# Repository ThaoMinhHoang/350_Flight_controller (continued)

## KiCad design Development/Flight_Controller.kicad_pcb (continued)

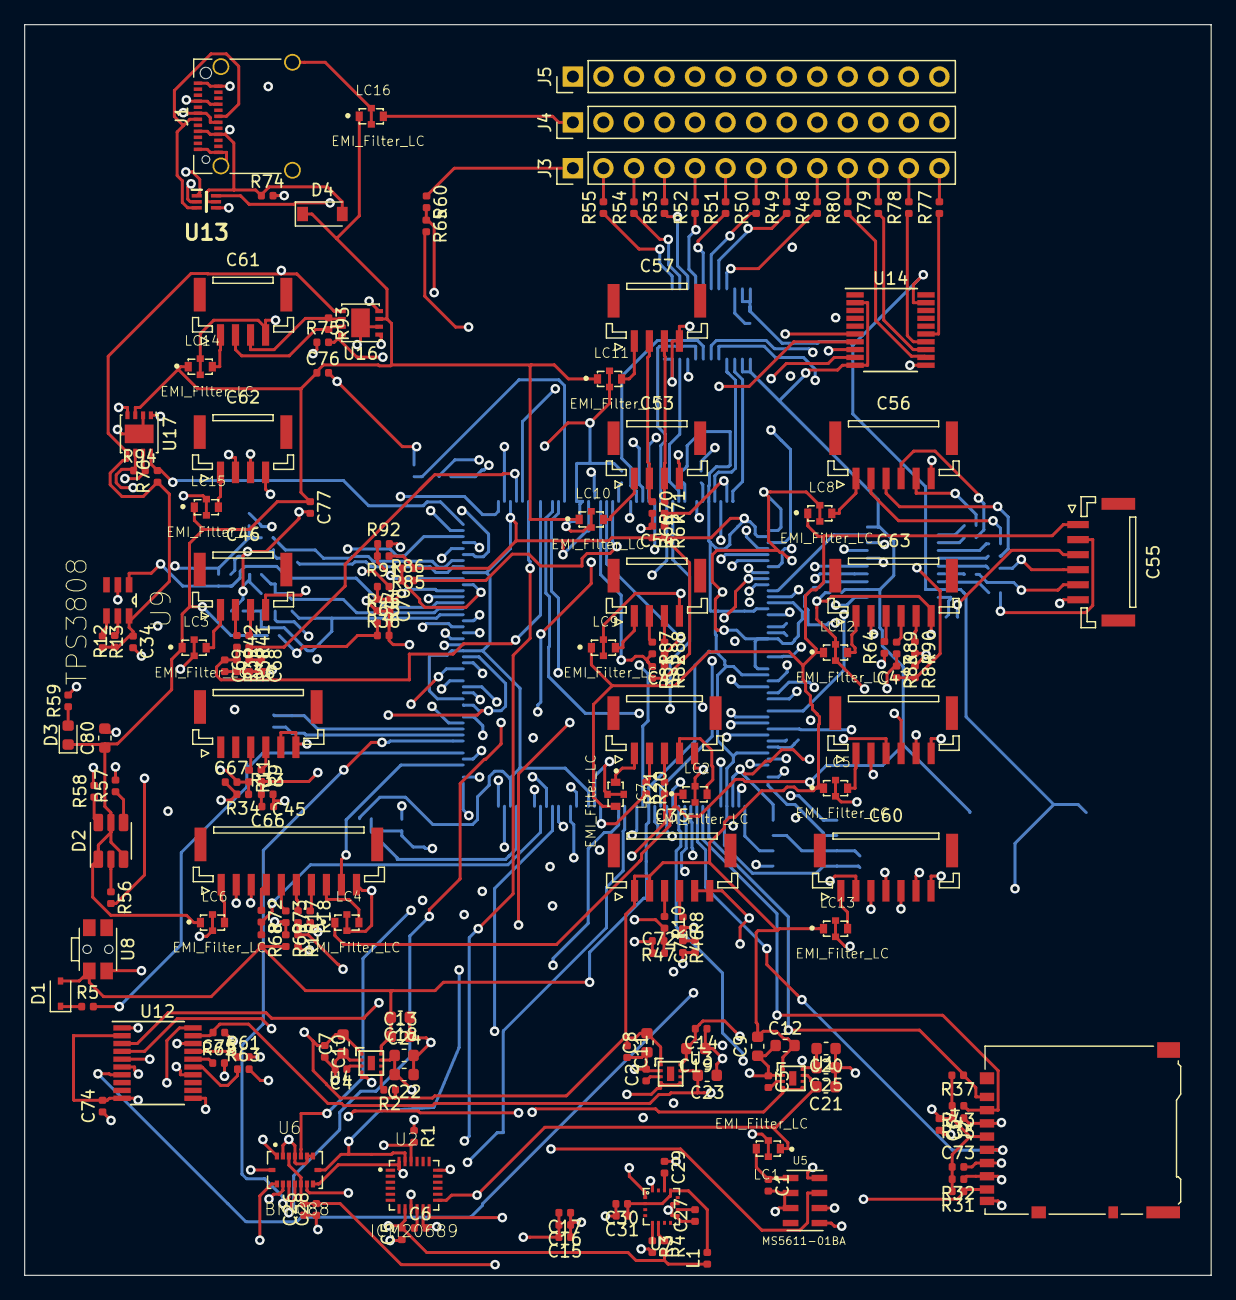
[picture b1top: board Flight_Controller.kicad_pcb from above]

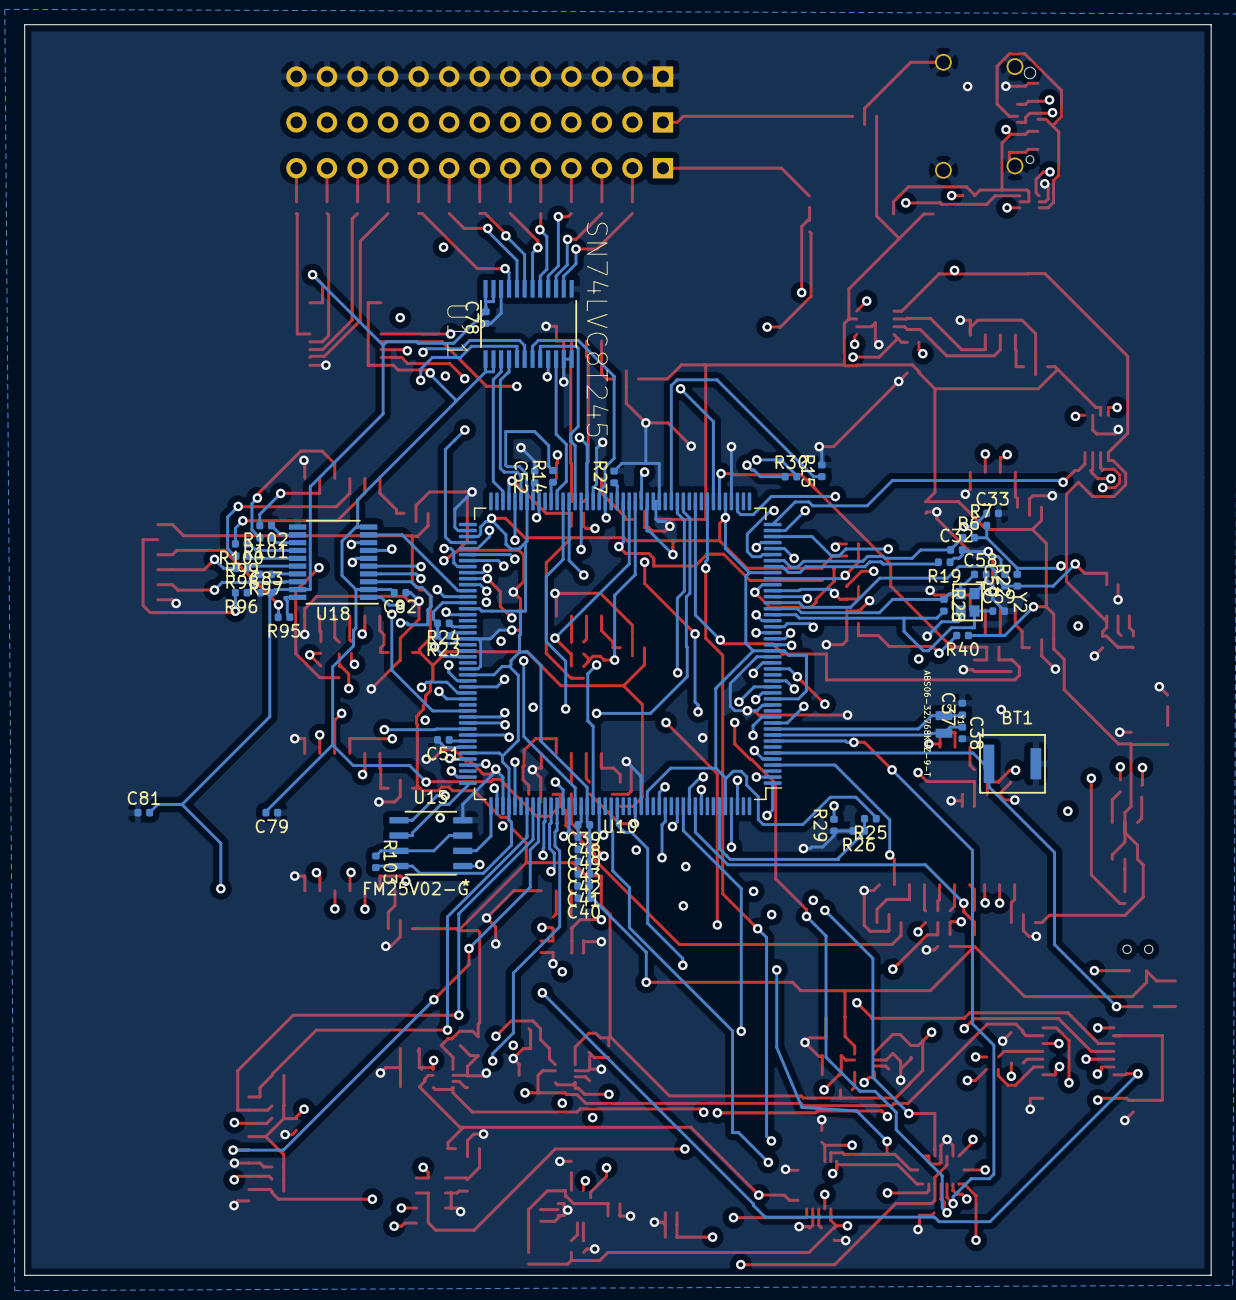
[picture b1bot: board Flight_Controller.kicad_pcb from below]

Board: 4 copper layers, 98.7 x 104.0 mm, 233 parts (52 on the bottom side), 236 nets.

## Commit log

2019-07-04 Create Magnetometer
2019-07-04 Magnetometer update
2019-07-05 Main Processor Update
2019-07-07 Update schematic to include all labels
2019-07-07 Added a couple of notes
2019-07-07 Added development schematics
    - Includes new connector symbols
    - Includes STM32F765IIT6 in schematic
    - Includes labeled connectors in schematic
2019-07-07 README revision
2019-07-15 Begun labelling connectors with pinout document
2019-08-01 ICM20689 Kidfile
2019-08-08 BMI088
2019-08-08 Power Supply
    Power supply for pixhawk 4 along with a few external power connectors and connections
2019-08-08 update IST8310, DPS422
2019-08-08 Hope for the best
2019-08-08 Hole for the best 2
2019-08-12 Updated Wiring
    - 3 Sensors connected, some might need to change. Definitely needs to be double-checked at some point.
    - All labels are now global
2019-08-12 Crystal oscillator circuit added
2019-08-13 wiring updates
2019-08-14 Updated power connections
    All power components have been connected to the appropriate places
2019-08-15 Organised layout of schematic
2019-08-21 Minor changes
2019-08-21 Sensor & FRAM Update
2019-08-22 Finished Sensors, Fixed PMU
2019-08-22 barometer update
2019-08-22 Finished FRAM, Added CHECK notes, Updated Osc.
2019-08-29 Massive Update
    - Sensors
    - Processor
    - Power Management
    - Peer Checking
    - Lots more
2019-08-31 Updates on footprints
    Missing footprints: connectors, sensors
2019-08-31 footprint lib
2019-09-02 Updated schematics, added USB-C Port, etc.
2019-09-02 Move footprints to main folder
2019-09-02 Added footprints
    Added footprints into dedicated library and applied to corresponding component
2019-09-03 Stability update, ensuring all files are up to date
2019-09-05 Feature Update!
    + Data Translation, CAN Bus, I2C Rail, ADC Rail
    + SD Card ready to merge
    + New Formatting (Clean up)
2019-09-05 Merged Status LED and SD Card
2019-09-05 Finished Ports
2019-09-05 Schematics 99% Finished
    + Double check capacitor values
    + Clarify VBAT connection
2019-09-05 Finished Schematics.
2019-09-05 Error Fixing
2019-09-05 + New Footprints, Started PCB
2019-09-14 footprint update
    Found in Newfootprint folder
2019-09-18 Complete footprints
2019-09-19 Connector Update
2019-09-19 Footprint Update
2019-09-19 PCB Started
2019-09-26 PCB layout edit
2019-09-26 PCB layout editting
2019-09-26 PCB Routing Update
2019-09-27 PCB Routing 27 Sep
2019-09-28 Added EMI LC Footprint
2019-09-28 PCB 4 layers, 89 unrouted
2019-09-29 Completed all PCB connections
2019-09-30 Shrunt PCB size to 100x100mm
2019-09-30 Shrunk PCB size to 100x100mm
2019-10-08 PCB GND Fill fix
    Hopefully it doesn't break this time..
2019-10-08 Updated some capacitor footprints
    Updated footprints from from 0402_1005 to 0603_1608, still need to do a lot more
2019-10-08 Completely updated capacitor footprints
2019-10-13 Fixed all PCB errors
    Ready to print!
